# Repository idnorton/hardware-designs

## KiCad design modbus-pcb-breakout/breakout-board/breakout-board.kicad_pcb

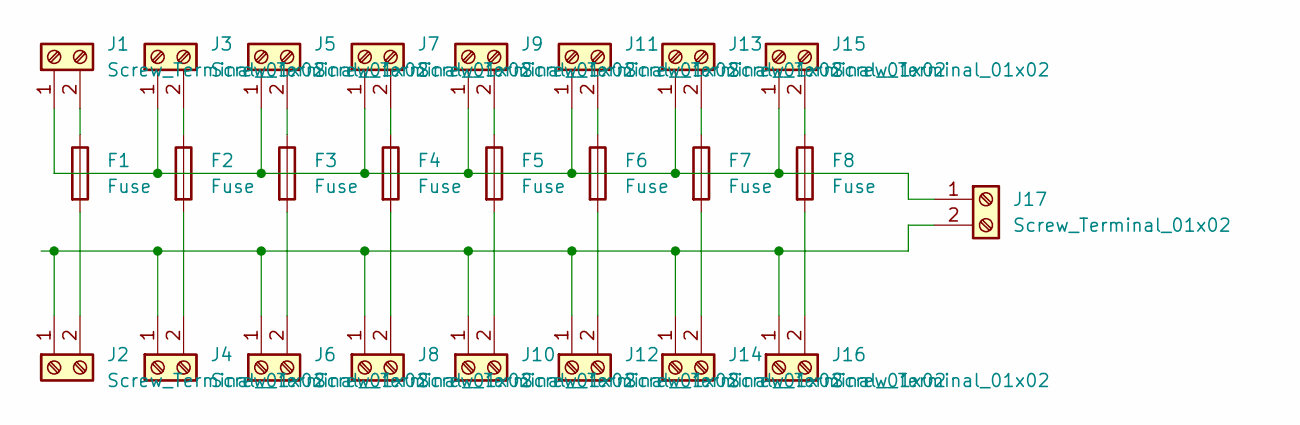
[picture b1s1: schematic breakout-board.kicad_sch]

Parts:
F1, F2, F3, F4, F5, F6, F7, F8: Fuse; Fuseholder_Blade_ATO_Littelfuse_Pudenz_2_Pin
J1, J2, J3, J4, J5, J6, J7, J8, J9, J10, J11, J12, J13, J14, J15, J16, J17: Screw_Terminal_01x02; PhoenixContact_MSTBVA_2,5_2-G_1x02_P5.00mm_Vertical

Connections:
unnamed: F1.1, J1.2
unnamed: F1.2, J2.2
unnamed: F2.1, J3.2
unnamed: F2.2, J4.2
unnamed: F3.1, J5.2
unnamed: F3.2, J6.2
unnamed: F4.1, J7.2
unnamed: F4.2, J8.2
unnamed: F5.1, J9.2
unnamed: F5.2, J10.2
unnamed: F6.1, J11.2
unnamed: F6.2, J12.2
unnamed: F7.1, J13.2
unnamed: F7.2, J14.2
unnamed: F8.1, J15.2
unnamed: F8.2, J16.2
unnamed: J1.1, J3.1, J5.1, J7.1, J9.1, J11.1, J13.1, J15.1, J17.1
unnamed: J2.1, J4.1, J6.1, J8.1, J10.1, J12.1, J14.1, J16.1, J17.2

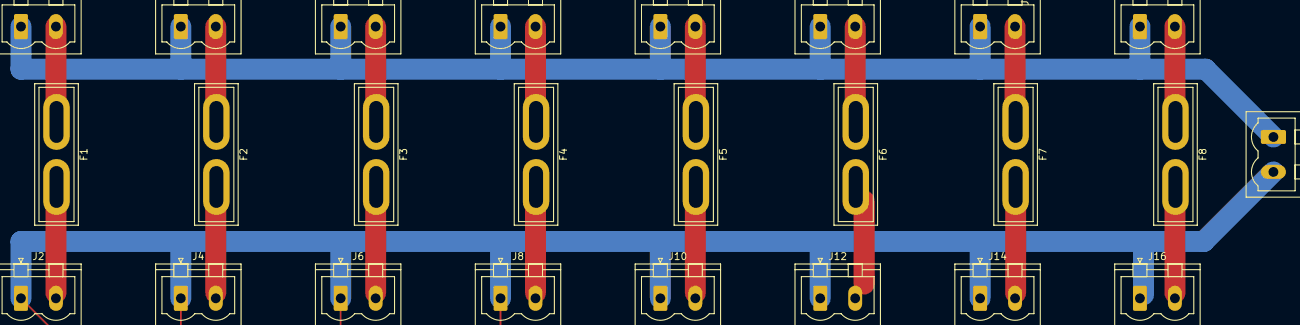
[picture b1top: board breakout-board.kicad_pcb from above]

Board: 2 copper layers, 25 parts (0 on the bottom side), 18 nets.

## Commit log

2017-03-07 Adding blast gate mk1
2017-03-08 Updating to sync design with mk2
2018-08-19 Add RepRapDiscount GLCD panel layout for OpenSCAD
2018-08-19 Fixup whitespace and naming inconsistencies
2018-08-19 Correcting rotary encoder dimension
2020-09-28 Adding cat climbing wall designs
2020-09-28 Adding name badge idea
2021-02-02 Adding corner wall box
2021-10-23 Add 750x250 wall board design
2021-10-23 Draft design for RGB flag
2022-02-18 Add chimney plug design
2022-02-21 Iterating design mk3 test fit
2022-03-01 Working insert and cap
2022-06-24 Adding gasket for lincat EB3F boiler
2022-07-24 Add first draft cat tree center
2022-07-27 Moving banner clamp design from private to public
2022-08-05 add test bolt
2022-08-10 Committing 20/15 test pieces
2022-09-11 Add B5 HW-5 boiler lid repair design
2022-09-14 Rework lid lip to be tapered
2022-09-14 Add stl to repo for viewing via github
2022-12-27 Add cat banister step
2022-12-27 Fixup wording
2022-12-27 Adding shelving drafts from laptop
2022-12-27 First draft can storage end
2023-01-14 Committing local changes
2023-01-15 Increase mounting hole offset to 103 to make it fit
2023-01-16 Add STL for final design
2023-01-16 Add tolerance gap for paint buildup
2023-01-16 Add stl file
2023-01-19 Adding updates to cat tube centre
2023-01-19 Add settings for tube centers
2023-01-19 Refactor files into a module
2023-01-20 Update stl files for tapered design
2023-01-20 Remove individual files and create module
2023-01-23 Refactor to add screw holes
2023-01-23 Update tube centers to include holes
2023-01-26 Add flange head for cap
2023-01-27 Add STL for 76mm endcap
2023-01-29 Add flange diameter parameter option
2023-01-30 Cleanup slt etc files to re-generate
2023-01-30 Add params for CLI use and fix flange dimensions
2023-02-01 Improve command line usage
    Add docs on usage
    Add option for screw diameter
    Change to using id (inner diameter) and od (outer diameter) to be clearer
2023-02-07 Update README
    Add note about Seam position
    Restructure to reduce duplication
    Add note on support materials
    Probably need to say something about flipping the part or do
    that in the code that generates the STL. Only relevant when
    it's an endcap otherwise not needed
2023-02-16 Add generic equipment bracket mounts
2023-04-05 Add parameterised vacuum nozzle adapter
2023-05-22 Move generated files to subdir
2023-05-22 Working bolt recess for behind the bracket
2023-07-13 Increase bolt diameter to make fit easier
2023-07-14 Commiting work in progress README
2023-07-14 Add Glastonbury photos from Russ
2023-07-14 Add picture of 3d printed brackets
2023-08-17 Adding test caraloc 400 surround
2023-12-07 Add work in progress socket set liner
2023-12-07 Test stl
2023-12-08 Reworking socket wrench to make it fit
2023-12-08 Reducing head diameters by 4mm
2023-12-14 Final design tweaks for full size print
2023-12-19 WIP sensio
2023-12-19 Add junction box design for Sensio profile
2023-12-21 Adding mounting plate
2023-12-21 Increase radius and fixup distance to back of box
2023-12-21 Adding STL for design
2023-12-21 Final version of door handle
2023-12-22 Fixup omission in quadrant function
    Handy if it uses the diameter value from the top of the file
    or you end up reprinting exactly the same part multiple times
    and wondering if it's the printer or you that's losing the
    limited quantity of available marbles
2024-01-06 Change mounting point design to be inline
    Switch from top mounted to mounted inline with the path of the profile.
    One fixed point screw and another slot to make it easier to slide the box
    onto the extrusion in place
    Move the cable hole to the side for invisble cable route
2024-01-07 Refactor to mirror and add supports
    * Change to module in order to have two instances one mirrored
    * Add lip into extrusion hole 5mm in to stop the extrusion going in further
    * Add support clips to the design
2024-01-18 Add bed brackets for Ikea LÖNSET
2024-01-18 Move brackets into van subdir
2024-01-20 Add screw holes
2024-01-21 Increase thickness to 4mm
2024-01-28 Adjustments based on test fit
    * Add 2mm tolerance to top and bottom sizing
    * Reduce height of top to 12mm
2024-01-28 Whitespace fixup
2024-01-28 Remove 3mf and gcode files
2024-01-28 Add 3mf and gcode files to git ignore
2024-02-01 Adding offset to allow alignment of top and bottom
2024-02-07 Adding more banner photos
2024-02-07 Adding STL files
2024-02-07 Adding links to new images
2024-03-20 Straight edge brackets only have one bed frame
2024-03-21 Offset holes -8 so they appear on both sides
    One side of the offset bracket top for the bed frame only has holes in one
    side of the bracket so offset by -8 to make sure it goes through both sides
2024-04-17 First outline stab at PCB box for modbus relay board
2024-04-18 Fixup floating platform and pins
2024-04-22 Add spacer design
2024-04-22 Update dimensions following test print
2024-04-22 Adjusting hole placement following test print
2024-07-07 Adding modbus PCB fuse breakout board
2024-09-08 Add first draft of kitchen storage unit
    Also adding aluminium extrusion library fork with 3060 support added
2024-09-08 Adding equipment brackets for meanwell PSU
2024-09-08 Removing binary file
2024-09-08 Draft Dewalt t-stak box insert footprint
2024-09-08 Adding link to original repo and licence
2024-09-08 Add cable hanger
    This seemed like a good idea until Will-H pointed out that we could just use a cable tie.... :)
2024-10-17 Reduce height to 845 to match Alex's worktops
2024-12-26 Add adapter bracket for Alex's bed
2024-12-26 Add stl for bed bracket for better rendering
2025-01-22 Adding PSU terminal enclosure start
2025-01-23 After a year in use, tweak parts
    Took the van apart ready to do the insulation and flooring so
    I have all of the parts in the house for the first time in ages.
    Taking the opportunity to tweak the design to make it better and
    also switch from using screws in the bed frams to clevis pins
    making this easier to keep secure but remove when needed.
    * Make the top taller
2025-01-29 Final version sent to 6h35m print...
2025-01-29 Dammit, missed the open file I hadn't saved
2025-01-29 Add print settings to source file
2025-03-18 Adjust Y hole positioning following test prints
2025-03-18 Removing binary files for breakout boards
2025-03-19 Adding battery spacer
2025-04-29 Updating fuse positions
2025-05-04 Add fuse and modbus panel
2025-05-04 Add mounting points and increased fusebox mounting holes
2025-05-07 More basic box rather than over complicating
2025-05-08 Drop wall to 5mm for test printage
2025-05-08 Add print settings
2025-05-08 Refactor to add wall supports and reduce base material
2025-05-16 Allow vertical scaling keeping gaps the same
2025-05-23 Mounting frame for fusebox with relays
2025-05-23 Attempt #3 adjusting dimensions more accurately
2025-05-23 Add lip to supports for lid and fix spacing
2025-05-23 Formatting cleanup, adding cover screw holes
2025-05-23 Reduce fn to make rendering faster
2025-05-24 Adding brackets for 24v PSU
2025-06-03 Add mount for Teyes camera
2025-06-07 Replace round boss holes with square, lower screw holes
2025-06-12 Tweak design for better fit
    Base was too thick for the screws
    Inset for bosses on camera was too deep resulting in it not sitting flat
2025-06-13 Switch from heat set insert to captive nut
2025-06-18 Dimension fiddling
    Better fit of the camera body
    Better fit on the nuts on the sides
    Slightly enlarge hole for side bolts
2025-06-18 Add chassis bracket for camera
2025-11-10 Add kitchen cabinet feet to repo
2025-12-07 Remove Bravilor B5 parts
    Not a sensible approach, not hygenic or temperature resistant
2025-12-15 Adding README for bed-bracket
2025-12-15 Changing to using a JS lib
2025-12-15 Switch to inline image
2025-12-15 Another approach
2026-03-02 Add busbar
2026-03-03 Reworking design to fix issues with v1
2026-03-04 Working model of terminal cover base
    Lots of iterations to fix little niggles around terminal placement
2026-04-11 Pre-commit repo cleanup
2026-04-12 Clean up existing bottom half add top
    * Remove hard coded value to variable 'cable_crimp_groove'
    * Add top half of the terminal cover
2026-04-12 Make bottom half busbar tabs longer
